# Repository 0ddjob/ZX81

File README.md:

# ZX81 Projects

## [ZX81 RAM Upgrade](RAM_Upgrade)
Simple plug-in 32KB RAM for ZX81 &amp; TS1000 using through-hole SRAM.  Expectation is that it's used with the very excellent [vLA81](https://www.vretrodesign.com/products/vla81-zx81-ula-replacement).<br>

{Fri 15-Sept-2023}<br>
Sent board prototype for fabrication<br>

## [ZX81 Centronics Interface](Centronics)
Redrawn from the original c't magazine schematic.<br>
{Sat 16-Sept-2023}<br>
Work in progress

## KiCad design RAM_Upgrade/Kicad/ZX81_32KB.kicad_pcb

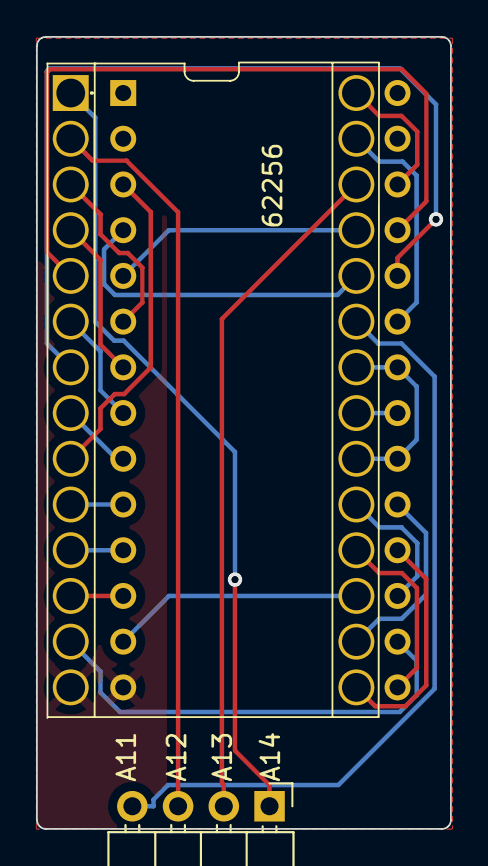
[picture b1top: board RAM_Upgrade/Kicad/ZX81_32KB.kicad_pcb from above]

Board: 2 copper layers, 23.0 x 44.0 mm, 3 parts (0 on the bottom side), 27 nets.

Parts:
IC1: CY62256NLL-55SNXI; DIP1587W140P254L3632H381Q28N
J3: Conn_01x04_Pin; PinHeader_1x04_P2.54mm_Horizontal
J4: 828-AG11D-LF; 828AG11DLF

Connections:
/+5V: IC1.28 (VCC), J4.26
/A00: IC1.10 (A0), J4.10
/A01: IC1.9 (A1), J4.3
/A02: IC1.8 (A2), J4.9
/A03: IC1.7 (A3), J4.24
/A04: IC1.6 (A4), J4.8
/A05: IC1.5 (A5), J4.25
/A06: IC1.4 (A6), J4.7
/A07: IC1.3 (A7), J4.6
/A08: IC1.25 (A8), J4.5
/A09: IC1.24 (A9), J4.4
/A10: IC1.21 (A10), J4.21
/A11: IC1.23 (A11), J3.4
/A12: IC1.2 (A12), J3.3
/A13: IC1.26 (A13), J3.2
/A14: IC1.1 (A14), J3.1
/D0: IC1.11 (DQ0), J4.11
/D1: IC1.12 (DQ1), J4.12
/D2: IC1.13 (DQ2), J4.16
/D3: IC1.15 (DQ3), J4.18
/D4: IC1.16 (DQ4), J4.19
/D5: IC1.17 (DQ5), J4.13
/D6: IC1.18 (DQ6), J4.15
/D7: IC1.19 (DQ7), J4.17
/GND: IC1.14 (VSS), J4.14
/~RAMCS: IC1.20 (CE#), IC1.22 (OE#), J4.20, J4.22
/~WR: IC1.27 (WE#), J4.23

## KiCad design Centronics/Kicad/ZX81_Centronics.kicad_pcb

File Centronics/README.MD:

# ZX81 Centronics Interface

Recreating a DIY centronics interface from German computer magazine c't.<br>

Google [auto-translation](ZX81_Centronics_Interface_p1.jpg) of the German.

[Redrawn schematic](ZX81_Centronics.pdf)

{17-Sept-2023}:<br>
Work in progress ... <br>

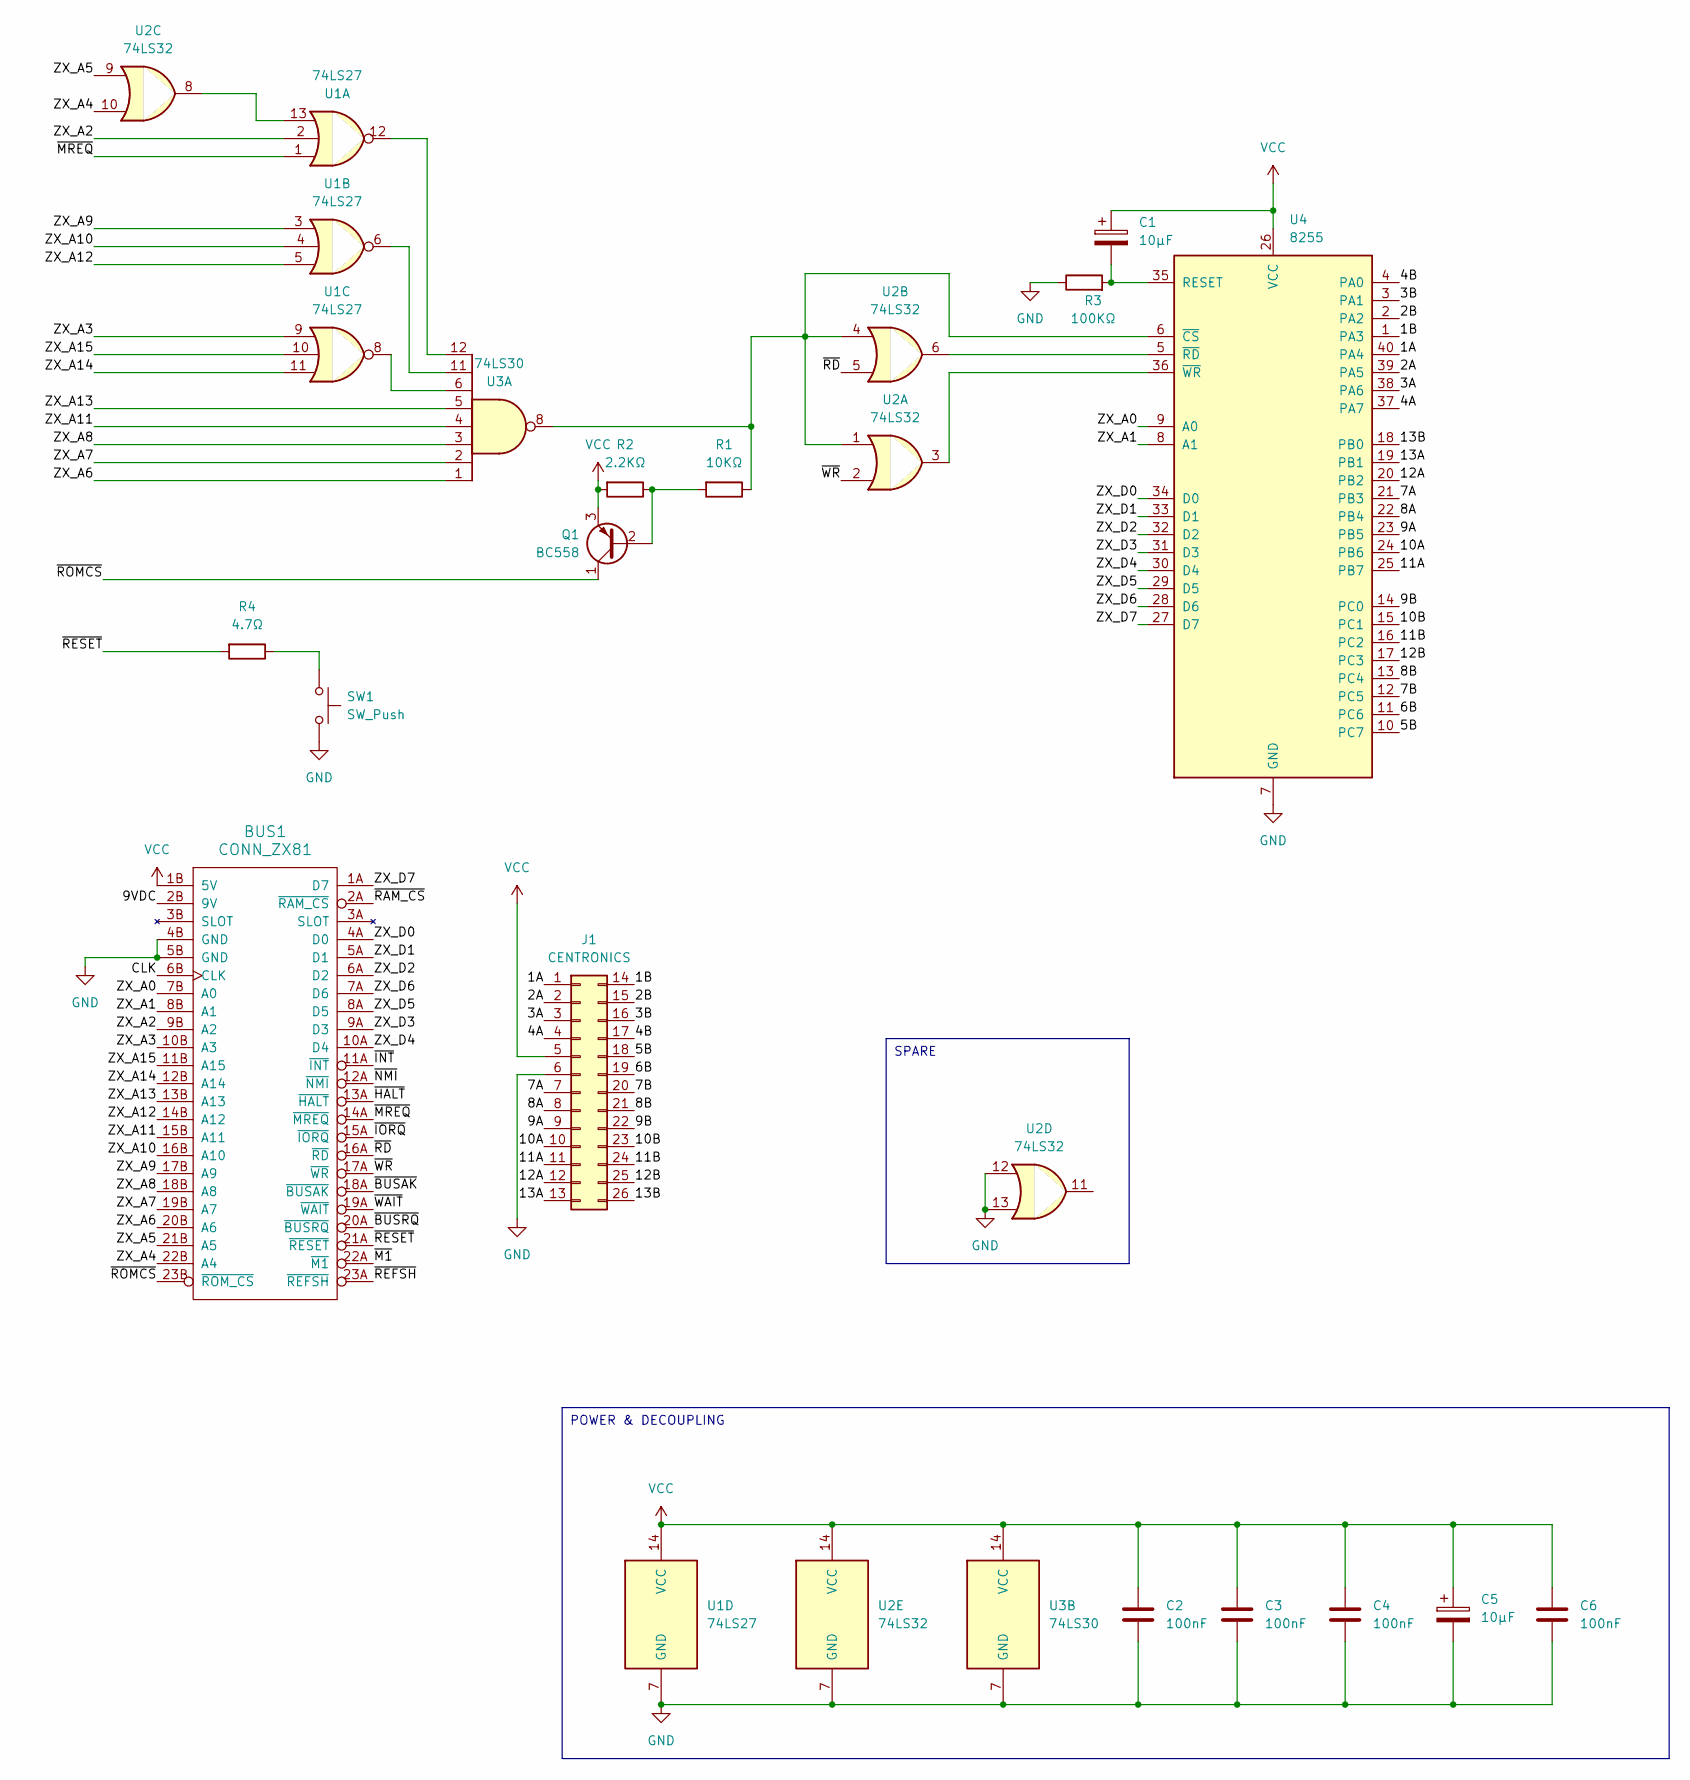
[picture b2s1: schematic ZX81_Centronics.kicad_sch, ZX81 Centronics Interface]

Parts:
BUS1: CONN_ZX81; ZX81_EDGE
C1, C5: 10µF; CP_Radial_D5.0mm_P2.50mm
C2, C3, C4, C6: 100nF; C_Disc_D4.3mm_W1.9mm_P5.00mm
J1: CENTRONICS; PinHeader_2x13_P2.54mm_Vertical
Q1: BC558; TO-92_Inline
R1: 10KΩ; R_Axial_DIN0207_L6.3mm_D2.5mm_P7.62mm_Horizontal
R2: 2.2KΩ; R_Axial_DIN0207_L6.3mm_D2.5mm_P7.62mm_Horizontal
R3: 100KΩ; R_Axial_DIN0207_L6.3mm_D2.5mm_P7.62mm_Horizontal
R4: 4.7Ω; R_Axial_DIN0207_L6.3mm_D2.5mm_P7.62mm_Horizontal
SW1: SW_Push; SW_PUSH_6mm_H4.3mm
U1: 74LS27; DIP-14_W7.62mm
U2: 74LS32; DIP-14_W7.62mm
U3: 74LS30; DIP-14_W7.62mm
U4: 8255; DIP-40_W15.24mm

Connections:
/1A: J1.1, U4.40 (PA4)
/1B: J1.14, U4.1 (PA3)
/2A: J1.2, U4.39 (PA5)
/2B: J1.15, U4.2 (PA2)
/3A: J1.3, U4.38 (PA6)
/3B: J1.16, U4.3 (PA1)
/4A: J1.4, U4.37 (PA7)
/4B: J1.17, U4.4 (PA0)
/5B: J1.18, U4.10 (PC7)
/6B: J1.19, U4.11 (PC6)
/7A: J1.7, U4.21 (PB3)
/7B: J1.20, U4.12 (PC5)
/8A: J1.8, U4.22 (PB4)
/8B: J1.21, U4.13 (PC4)
/9A: J1.9, U4.23 (PB5)
/9B: J1.22, U4.14 (PC0)
/9VDC: BUS1.2B (9V)
/10A: J1.10, U4.24 (PB6)
/10B: J1.23, U4.15 (PC1)
/11A: J1.11, U4.25 (PB7)
/11B: J1.24, U4.16 (PC2)
/12A: J1.12, U4.20 (PB2)
/12B: J1.25, U4.17 (PC3)
/13A: J1.13, U4.19 (PB1)
/13B: J1.26, U4.18 (PB0)
/CLK: BUS1.6B (CLK)
/ZX_A0: BUS1.7B (A0), U4.9 (A0)
/ZX_A1: BUS1.8B (A1), U4.8 (A1)
/ZX_A2: BUS1.9B (A2), U1.2
/ZX_A3: BUS1.10B (A3), U1.9
/ZX_A4: BUS1.22B (A4), U2.10
/ZX_A5: BUS1.21B (A5), U2.9
/ZX_A6: BUS1.20B (A6), U3.1
/ZX_A7: BUS1.19B (A7), U3.2
/ZX_A8: BUS1.18B (A8), U3.3
/ZX_A9: BUS1.17B (A9), U1.3
/ZX_A10: BUS1.16B (A10), U1.4
/ZX_A11: BUS1.15B (A11), U3.4
/ZX_A12: BUS1.14B (A12), U1.5
/ZX_A13: BUS1.13B (A13), U3.5
/ZX_A14: BUS1.12B (A14), U1.11
/ZX_A15: BUS1.11B (A15), U1.10
/ZX_D0: BUS1.4A (D0), U4.34 (D0)
/ZX_D1: BUS1.5A (D1), U4.33 (D1)
/ZX_D2: BUS1.6A (D2), U4.32 (D2)
/ZX_D3: BUS1.9A (D3), U4.31 (D3)
/ZX_D4: BUS1.10A (D4), U4.30 (D4)
/ZX_D5: BUS1.8A (D5), U4.29 (D5)
/ZX_D6: BUS1.7A (D6), U4.28 (D6)
/ZX_D7: BUS1.1A (D7), U4.27 (D7)
/~BUSAK: BUS1.18A (~BUSAK)
/~BUSRQ: BUS1.20A (~BUSRQ)
/~HALT: BUS1.13A (~HALT)
/~INT: BUS1.11A (~INT)
/~IORQ: BUS1.15A (~IORQ)
/~M1: BUS1.22A (~M1)
/~MREQ: BUS1.14A (~MREQ), U1.1
/~NMI: BUS1.12A (~NMI)
/~RAM_CS: BUS1.2A (~RAM_CS)
/~RD: BUS1.16A (~RD), U2.5
/~REFSH: BUS1.23A (~REFSH)
/~RESET: BUS1.21A (~RESET), R4.2
/~ROMCS: BUS1.23B (~ROM_CS), Q1.1 (C)
/~WAIT: BUS1.19A (~WAIT)
/~WR: BUS1.17A (~WR), U2.2
GND: BUS1.4B (GND), BUS1.5B (GND), C2.2, C3.2, C4.2, C5.2, C6.2, J1.6, R3.1, SW1.2, U1.7 (GND), U2.7 (GND), U2.12, U2.13, U3.7 (GND), U4.7 (GND)
unnamed: Q1.2 (B), R1.2, R2.1
unnamed: R4.1, SW1.1
unnamed: U1.6, U3.11
unnamed: U1.8, U3.6
unnamed: U1.12, U3.12
unnamed: U1.13, U2.8
unnamed: C1.2, R3.2, U4.35 (RESET)
unnamed: R1.1, U2.1, U2.4, U3.8, U4.6 (~CS)
unnamed: U2.6, U4.5 (~RD)
unnamed: U2.3, U4.36 (~WR)
VCC: BUS1.1B (5V), C1.1, C2.1, C3.1, C4.1, C5.1, C6.1, J1.5, Q1.3 (E), R2.2, U1.14 (VCC), U2.14 (VCC), U3.14 (VCC), U4.26 (VCC)

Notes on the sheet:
SPARE
POWER & DECOUPLING

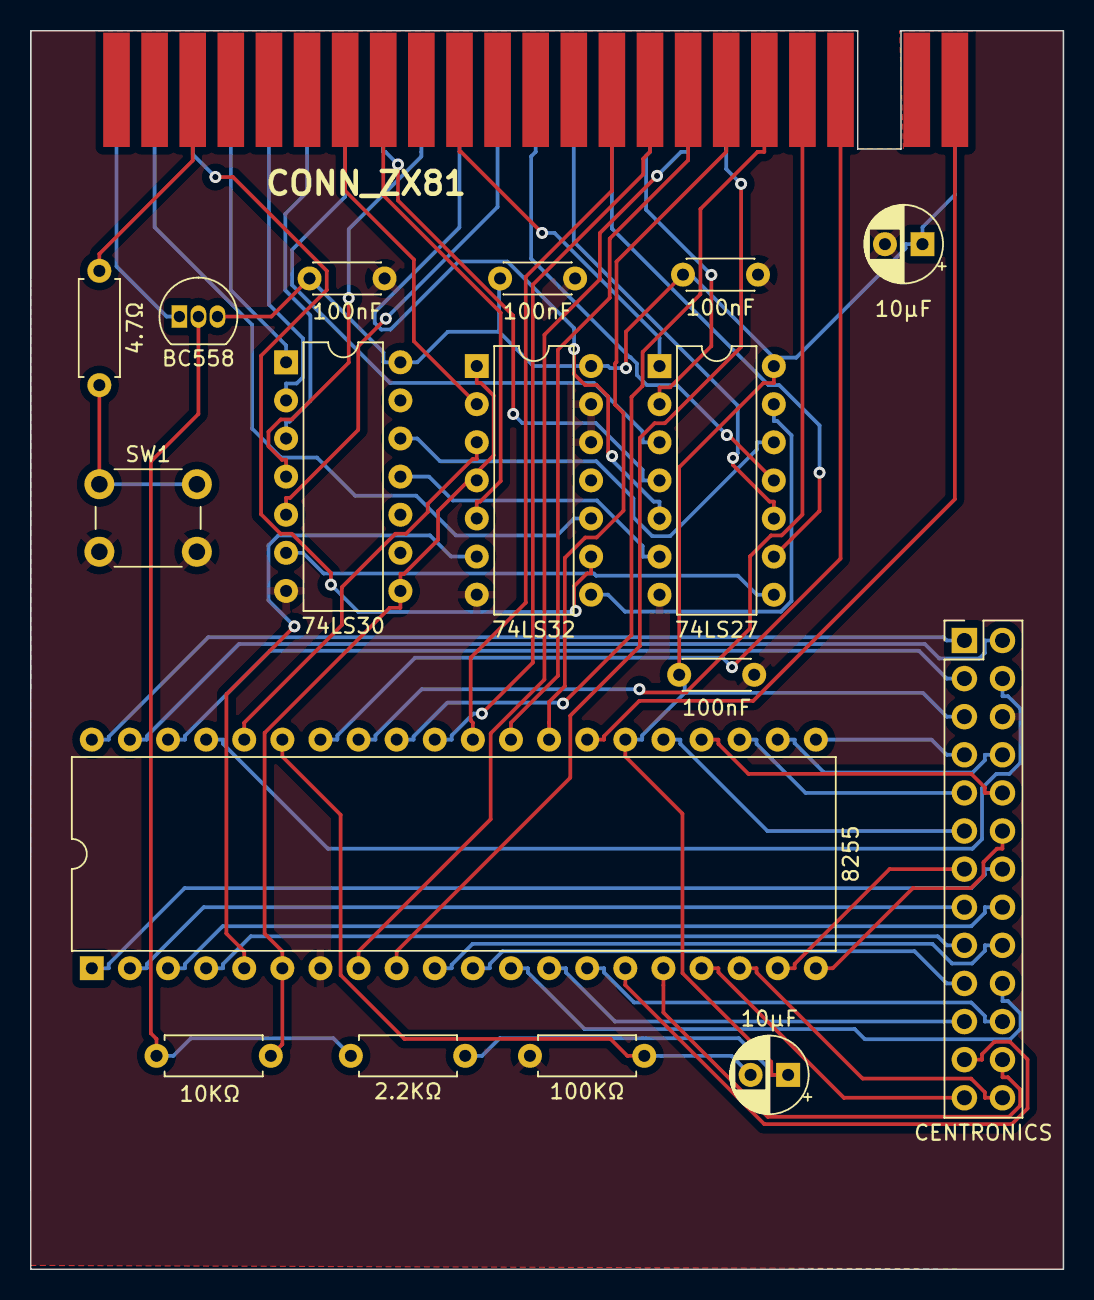
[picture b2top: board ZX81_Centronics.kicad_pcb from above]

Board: 2 copper layers, 68.8 x 82.5 mm, 18 parts (0 on the bottom side), 65 nets.

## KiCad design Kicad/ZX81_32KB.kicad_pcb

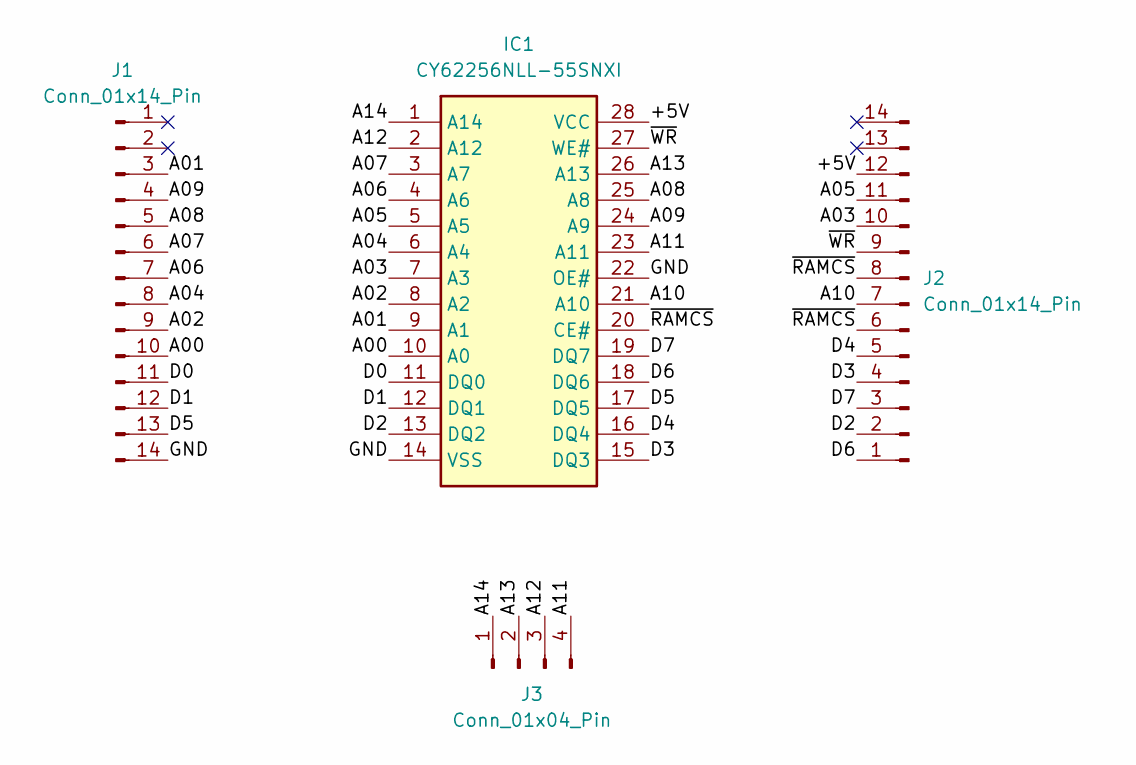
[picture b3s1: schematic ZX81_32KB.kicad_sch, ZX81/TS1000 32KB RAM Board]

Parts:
IC1: CY62256NLL-55SNXI; DIP1587W140P254L3632H381Q28N; Mouser Part Number 913-AS6C62256-55PCN
J1, J2: Conn_01x14_Pin; PinHeader_1x14_P2.54mm_Vertical
J3: Conn_01x04_Pin; PinHeader_1x04_P2.54mm_Horizontal

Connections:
/+5V: IC1.28 (VCC), J2.12
/A00: IC1.10 (A0), J1.10
/A01: IC1.9 (A1), J1.3
/A02: IC1.8 (A2), J1.9
/A03: IC1.7 (A3), J2.10
/A04: IC1.6 (A4), J1.8
/A05: IC1.5 (A5), J2.11
/A06: IC1.4 (A6), J1.7
/A07: IC1.3 (A7), J1.6
/A08: IC1.25 (A8), J1.5
/A09: IC1.24 (A9), J1.4
/A10: IC1.21 (A10), J2.7
/A11: IC1.23 (A11), J3.4
/A12: IC1.2 (A12), J3.3
/A13: IC1.26 (A13), J3.2
/A14: IC1.1 (A14), J3.1
/D0: IC1.11 (DQ0), J1.11
/D1: IC1.12 (DQ1), J1.12
/D2: IC1.13 (DQ2), J2.2
/D3: IC1.15 (DQ3), J2.4
/D4: IC1.16 (DQ4), J2.5
/D5: IC1.17 (DQ5), J1.13
/D6: IC1.18 (DQ6), J2.1
/D7: IC1.19 (DQ7), J2.3
/GND: IC1.14 (VSS), IC1.22 (OE#), J1.14
/~RAMCS: IC1.20 (CE#), J2.6, J2.8
/~WR: IC1.27 (WE#), J2.9

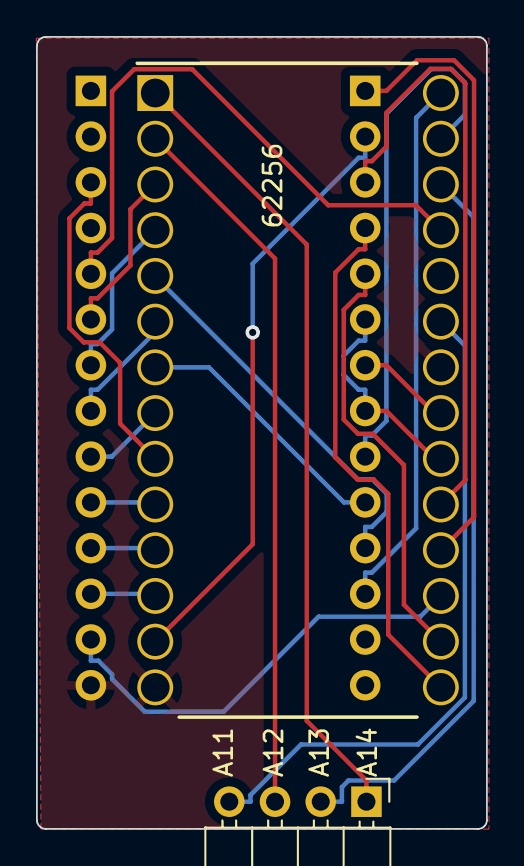
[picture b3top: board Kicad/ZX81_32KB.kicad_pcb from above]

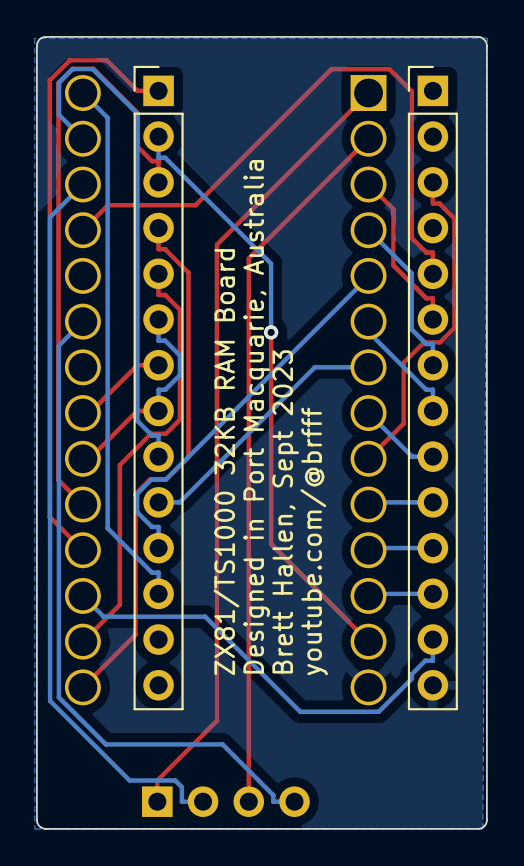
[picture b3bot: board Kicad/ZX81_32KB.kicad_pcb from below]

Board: 2 copper layers, 25.0 x 44.0 mm, 4 parts (2 on the bottom side), 27 nets.

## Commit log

2023-09-09 Work in progress
2023-09-10 Initial version
2023-09-10 Folder move
2023-09-10 Added PCB render
2023-09-10 Refinements
2023-09-16 Adjust folders
2023-09-16 Initial
2023-09-16 Basic schematic finished
2023-09-16 Added images
2023-09-17 Added English auto-translation
2023-09-17 Updated schematic plot
2023-09-17 Moved schematic
2023-09-17 Generated Gerber files
2023-10-16 Corrected initial version
2023-10-18 Original design
2023-10-18 Revert to original design
